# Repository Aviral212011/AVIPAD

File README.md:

this is a custom  macropad pcb  which has 8 eight  switches and a rotatry encoder . this can be use to make the things simple and to have fun !!! . this is fully made by Aviral :) .
this pcb is built in Build guild delhi in the supervision of organisers .

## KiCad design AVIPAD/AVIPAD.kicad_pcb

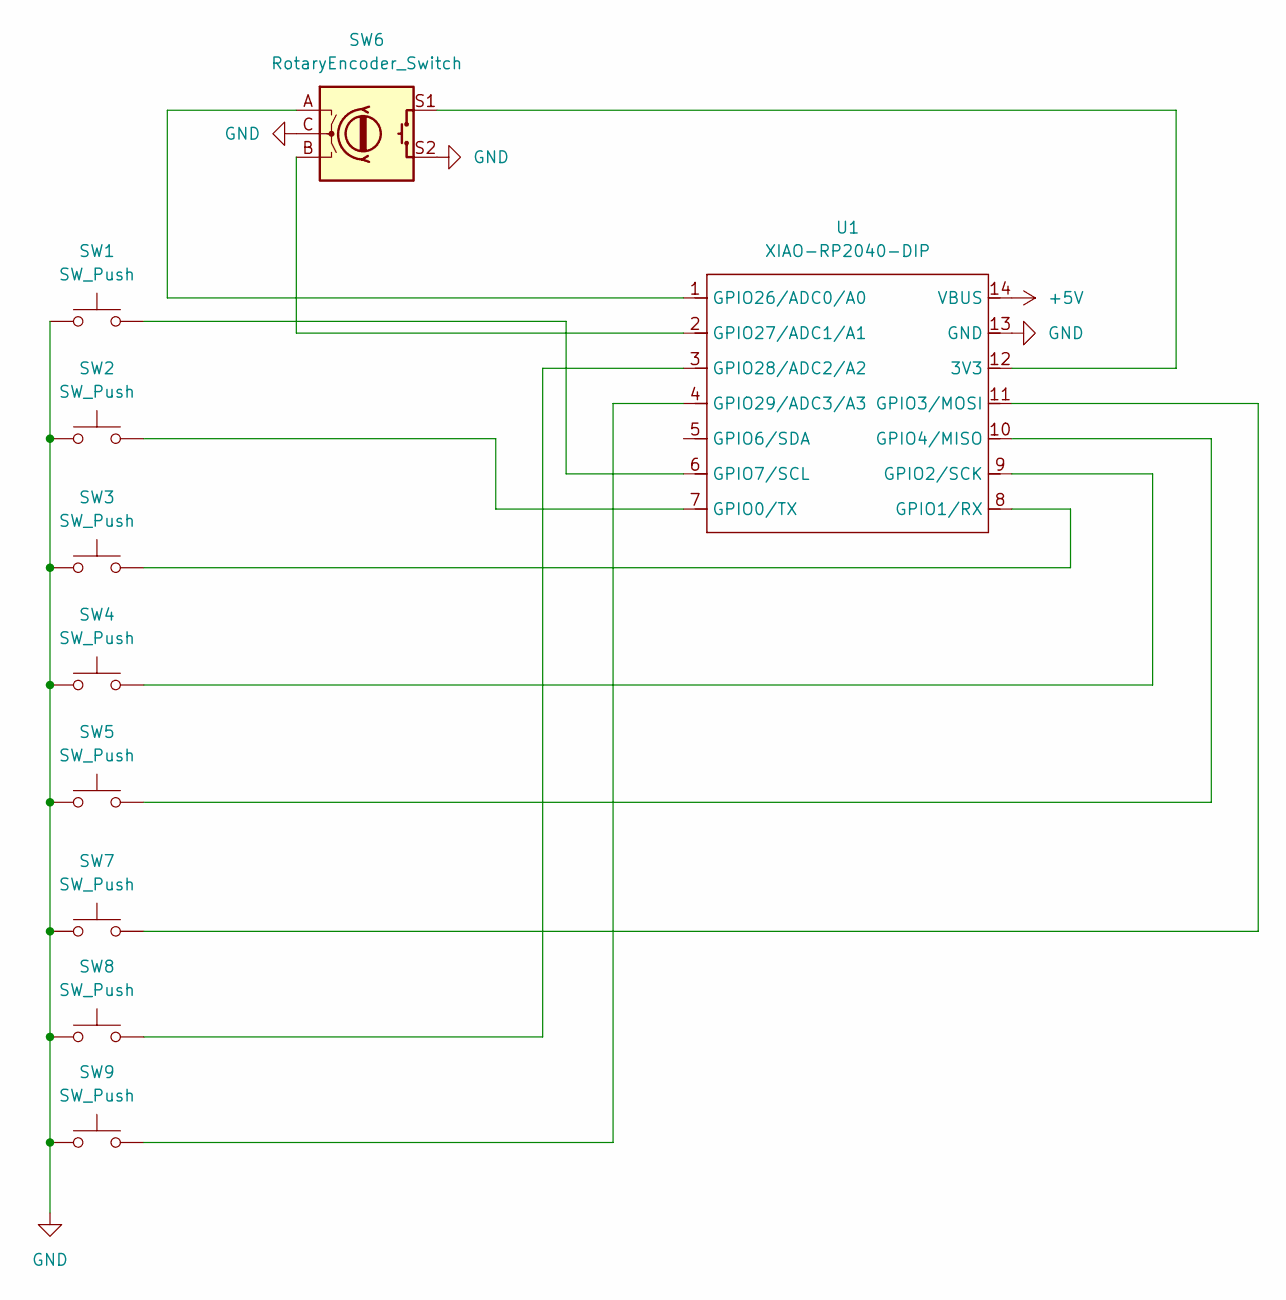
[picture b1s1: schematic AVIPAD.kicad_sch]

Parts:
SW1, SW2, SW3, SW4, SW5, SW7, SW8, SW9: SW_Push; SW_Cherry_MX_1.00u_PCB
SW6: RotaryEncoder_Switch; RotaryEncoder_Alps_EC11E-Switch_Vertical_H20mm_CircularMoun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
U1: XIAO-RP2040-DIP

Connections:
+5V: U1.14 (VBUS)
GND: SW1.1, SW2.1, SW3.1, SW4.1, SW5.1, SW6.C, SW6.S2, SW7.1, SW8.1, SW9.1, U1.13 (GND)
unnamed: SW6.S1, U1.12 (3V3)
unnamed: SW2.2, U1.7 (GPIO0/TX)
unnamed: SW3.2, U1.8 (GPIO1/RX)
unnamed: SW4.2, U1.9 (GPIO2/SCK)
unnamed: SW7.2, U1.11 (GPIO3/MOSI)
unnamed: SW5.2, U1.10 (GPIO4/MISO)
unnamed: SW1.2, U1.6 (GPIO7/SCL)
unnamed: SW6.A, U1.1 (GPIO26/ADC0/A0)
unnamed: SW6.B, U1.2 (GPIO27/ADC1/A1)
unnamed: SW8.2, U1.3 (GPIO28/ADC2/A2)
unnamed: SW9.2, U1.4 (GPIO29/ADC3/A3)

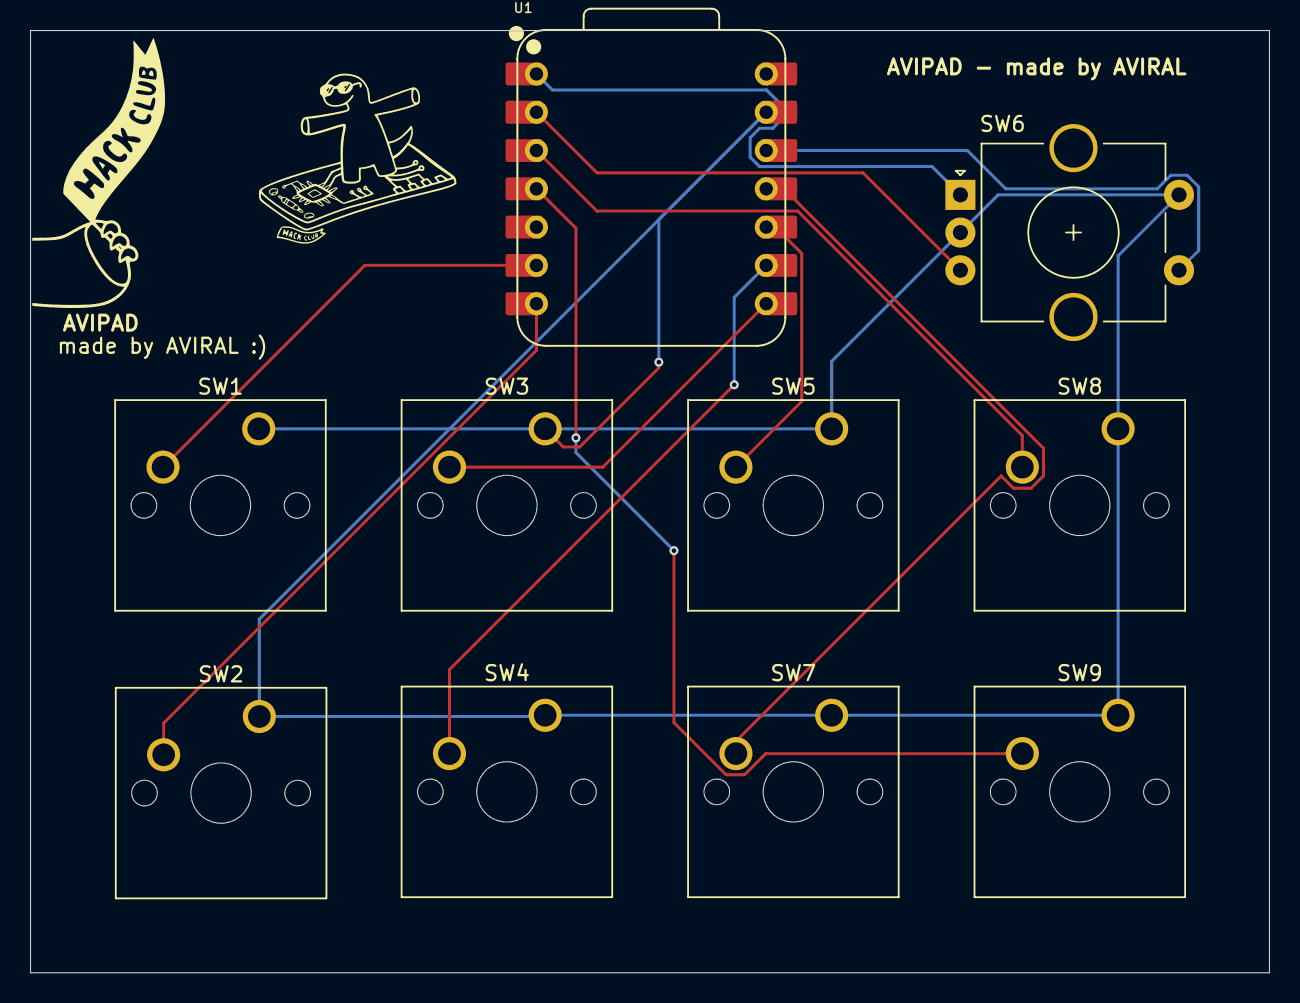
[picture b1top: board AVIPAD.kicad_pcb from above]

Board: 2 copper layers, 82.2 x 62.5 mm, 10 parts (0 on the bottom side), 12 nets.
